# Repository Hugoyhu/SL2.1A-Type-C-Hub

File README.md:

# SL2.1A Type-C Hub
A simple 4-port USB2 hub based on the SL2.1A design.
This board is designed in KiCAD v7! It is based off an earlier [2021 design](https://github.com/Hugoyhu/Hack-Club-Zephyr-USB-Hub) with USB-A outputs. 

This revises the board to provide USB2 Type-C outputs. By default, the schematic provides circuitry for default USB power (500mA) but resistor values can be changed to provide higher output current if available through external power. 

These boards have been built and tested.

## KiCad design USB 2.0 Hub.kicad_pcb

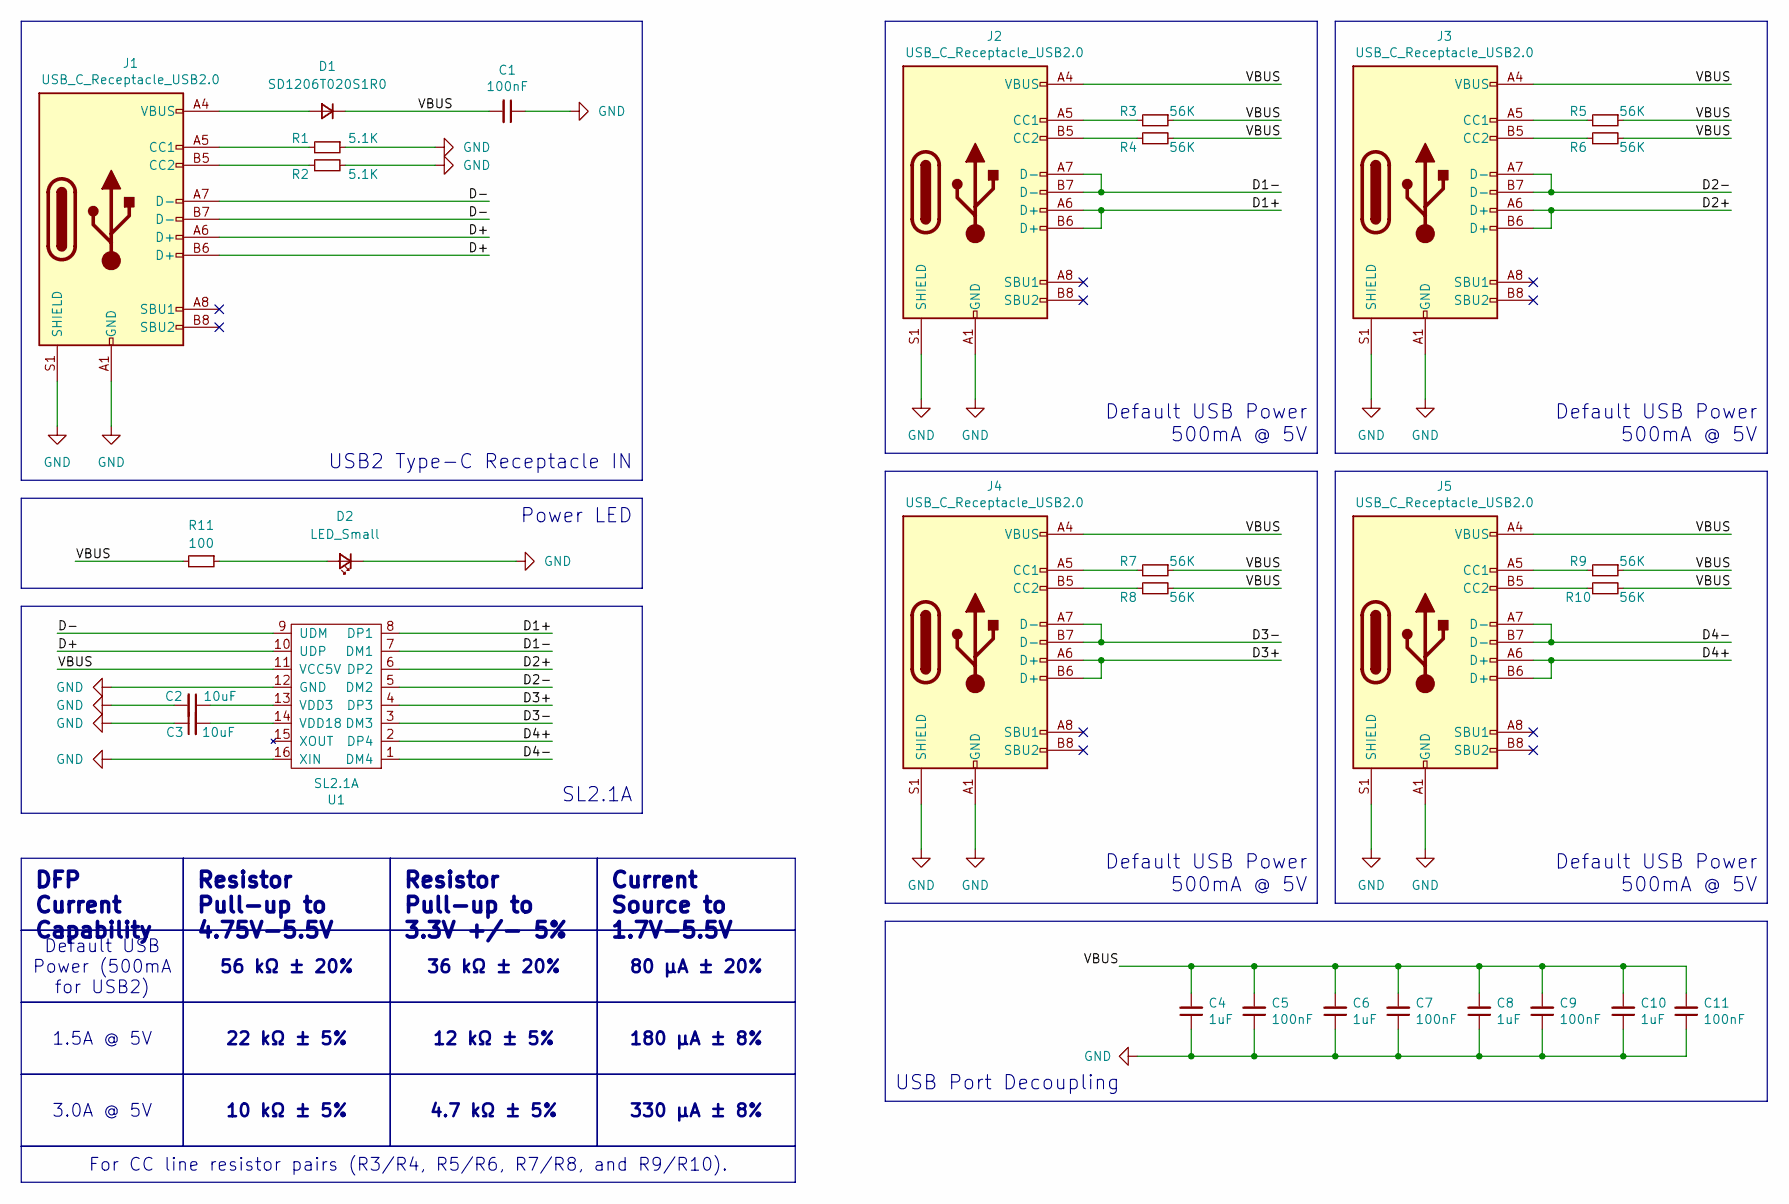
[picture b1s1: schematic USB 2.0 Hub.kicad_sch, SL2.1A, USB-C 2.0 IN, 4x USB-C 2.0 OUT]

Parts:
C1, C5, C7, C9, C11: 100nF; C_0805_2012Metric_Pad1.18x1.45mm_HandSolder
C2, C3: 10uF; C_0805_2012Metric_Pad1.18x1.45mm_HandSolder
C4, C6, C8, C10: 1uF; C_0805_2012Metric_Pad1.18x1.45mm_HandSolder
D1: SD1206T020S1R0; D_1206_3216Metric_Pad1.42x1.75mm_HandSolder
D2: LED_Small; LED_1206_3216Metric_Pad1.42x1.75mm_HandSolder
J1, J2, J3, J4, J5: USB_C_Receptacle_USB2.0; USB_C_Receptacle_HRO_TYPE-C-31-M-12
R1, R2: 5.1K; R_0805_2012Metric_Pad1.20x1.40mm_HandSolder
R3, R4, R5, R6, R7, R8, R9, R10: 56K; R_0805_2012Metric_Pad1.20x1.40mm_HandSolder
R11: 100; R_0805_2012Metric_Pad1.20x1.40mm_HandSolder
U1: SL2.1A; SOIC-16_4.55x10.3mm_P1.27mm

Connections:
/D1+: J2.A6 (D+), J2.B6 (D+), U1.8 (DP1)
/D1-: J2.A7 (D-), J2.B7 (D-), U1.7 (DM1)
/D2+: J3.A6 (D+), J3.B6 (D+), U1.6 (DP2)
/D2-: J3.A7 (D-), J3.B7 (D-), U1.5 (DM2)
/D3+: J4.A6 (D+), J4.B6 (D+), U1.4 (DP3)
/D3-: J4.A7 (D-), J4.B7 (D-), U1.3 (DM3)
/D4+: J5.A6 (D+), J5.B6 (D+), U1.2 (DP4)
/D4-: J5.A7 (D-), J5.B7 (D-), U1.1 (DM4)
/D+: J1.A6 (D+), J1.B6 (D+), U1.10 (UDP)
/D-: J1.A7 (D-), J1.B7 (D-), U1.9 (UDM)
/VBUS: C1.2, C4.2, C5.2, C6.2, C7.2, C8.2, C9.2, C10.2, C11.2, D1.1 (K), J2.A4 (VBUS), J2.A9 (VBUS), J2.B4 (VBUS), J2.B9 (VBUS), J3.A4 (VBUS), J3.A9 (VBUS), J3.B4 (VBUS), J3.B9 (VBUS), J4.A4 (VBUS), J4.A9 (VBUS), J4.B4 (VBUS), J4.B9 (VBUS), J5.A4 (VBUS), J5.A9 (VBUS), J5.B4 (VBUS), J5.B9 (VBUS), R3.1, R4.2, R5.1, R6.2, R7.1, R8.2, R9.1, R10.2, R11.2, U1.11 (VCC5V)
GND: C1.1, C2.2, C3.1, C4.1, C5.1, C6.1, C7.1, C8.1, C9.1, C10.1, C11.1, D2.1 (K), J1.A1 (GND), J1.A12 (GND), J1.B1 (GND), J1.B12 (GND), J1.S1 (SHIELD), J2.A1 (GND), J2.A12 (GND), J2.B1 (GND), J2.B12 (GND), J2.S1 (SHIELD), J3.A1 (GND), J3.A12 (GND), J3.B1 (GND), J3.B12 (GND), J3.S1 (SHIELD), J4.A1 (GND), J4.A12 (GND), J4.B1 (GND), J4.B12 (GND), J4.S1 (SHIELD), J5.A1 (GND), J5.A12 (GND), J5.B1 (GND), J5.B12 (GND), J5.S1 (SHIELD), R1.1, R2.2, U1.12 (GND), U1.16 (XIN)
unnamed: D1.2 (A), J1.A4 (VBUS), J1.A9 (VBUS), J1.B4 (VBUS), J1.B9 (VBUS)
unnamed: D2.2 (A), R11.1
unnamed: J1.A5 (CC1), R1.2
unnamed: J1.B5 (CC2), R2.1
unnamed: J2.A5 (CC1), R3.2
unnamed: J2.B5 (CC2), R4.1
unnamed: J3.A5 (CC1), R5.2
unnamed: J3.B5 (CC2), R6.1
unnamed: J4.A5 (CC1), R7.2
unnamed: J4.B5 (CC2), R8.1
unnamed: J5.A5 (CC1), R9.2
unnamed: J5.B5 (CC2), R10.1
unnamed: C2.1, U1.13 (VDD3)
unnamed: C3.2, U1.14 (VDD18)

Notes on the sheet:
Resistor Pull-up to 4.75V-5.5V
For CC line resistor pairs (R3/R4, R5/R6, R7/R8, and R9/R10).
22 kΩ ± 5%
12 kΩ ± 5%
330 μA ± 8%
Current Source to 1.7V-5.5V
4.7 kΩ ± 5%
36 kΩ ± 20%
DFP Current Capability
56 kΩ ± 20%
80 μA ± 20%
Resistor Pull-up to 3.3V +/- 5%
180 μA ± 8%
1.5A @ 5V
10 kΩ ± 5%
3.0A @ 5V
Default USB Power (500mA for USB2)
SL2.1A
Default USB Power 500mA @ 5V
USB2 Type-C Receptacle IN
USB Port Decoupling
Power LED

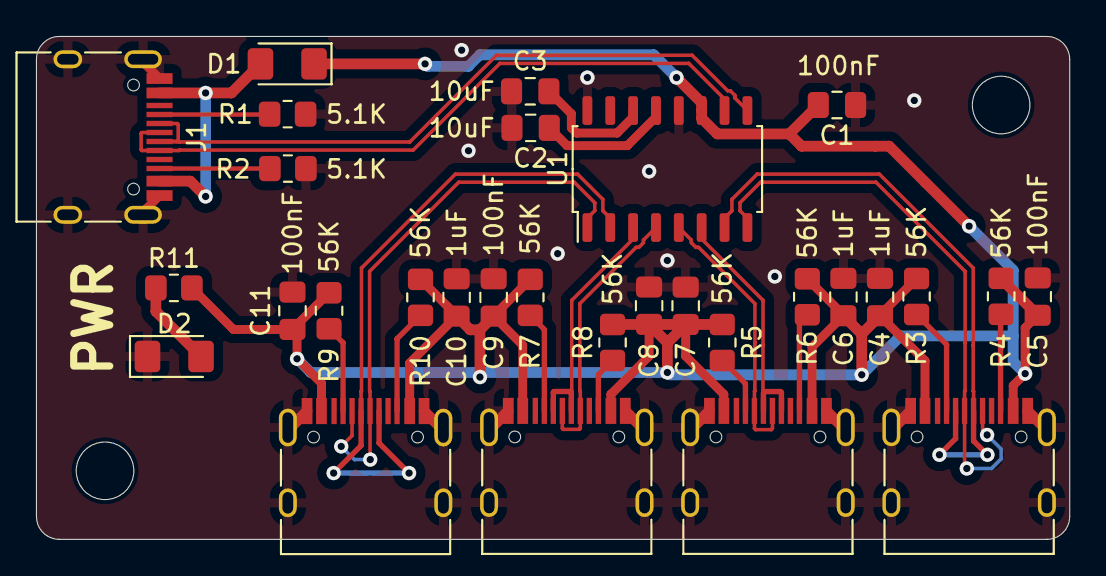
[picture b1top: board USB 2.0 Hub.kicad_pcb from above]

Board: 2 copper layers, 57.4 x 27.9 mm, 30 parts (0 on the bottom side), 26 nets.
